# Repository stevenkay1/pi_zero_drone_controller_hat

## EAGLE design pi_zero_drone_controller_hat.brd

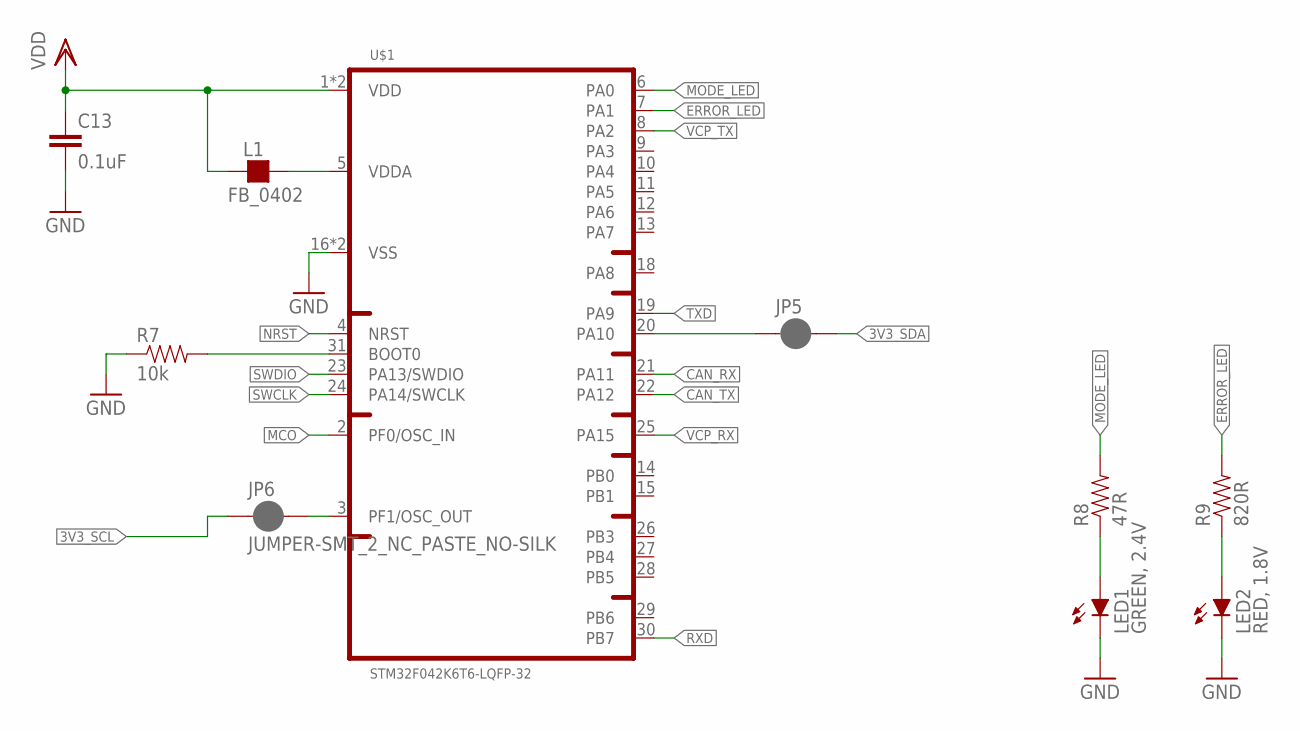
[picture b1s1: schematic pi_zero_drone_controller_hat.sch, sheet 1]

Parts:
C13: 0.1uF; 0402
JP5, JP6: JUMPER-SMT_2_NC_PASTE_NO-SILK; SMT-JUMPER_2_NC_PASTE_NO-SILK
L1: FB_0402; L0402
LED1: GREEN, 2.4V; CHIP-LED0603
LED2: RED, 1.8V; CHIP-LED0603
R7: 10k; RES_0402
R8: 47R; RES_0402
R9: 820R; RES_0402
U$1: STM32F042K6T6-LQFP-32; LQFP-32

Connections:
3V3_SCL: JP6.1; also elsewhere on the board
3V3_SDA: JP5.2; also elsewhere on the board
CAN_RX: U$1.21 (PA11)
CAN_TX: U$1.22 (PA12)
ERROR_LED: R9.2, U$1.7 (PA1)
GND: C13.2, LED1.C, LED2.C, R7.1, U$1.16 (VSS), U$1.32 (VSS); also elsewhere on the board
MCO: U$1.2 (PF0/OSC_IN)
MODE_LED: R8.2, U$1.6 (PA0)
unnamed: R7.2, U$1.31 (BOOT0)
unnamed: L1.2, U$1.5 (VDDA)
unnamed: JP5.1, U$1.20 (PA10)
unnamed: JP6.2, U$1.3 (PF1/OSC_OUT)
unnamed: LED2.A, R9.1
unnamed: LED1.A, R8.1
NRST: U$1.4 (NRST); also elsewhere on the board
RXD: U$1.30 (PB7); also elsewhere on the board
SWCLK: U$1.24 (PA14/SWCLK); also elsewhere on the board
SWDIO: U$1.23 (PA13/SWDIO); also elsewhere on the board
TXD: U$1.19 (PA9); also elsewhere on the board
VCP_RX: U$1.25 (PA15); also elsewhere on the board
VCP_TX: U$1.8 (PA2); also elsewhere on the board
VDD: C13.1, L1.1, U$1.1 (VDD), U$1.17 (VDD); also elsewhere on the board

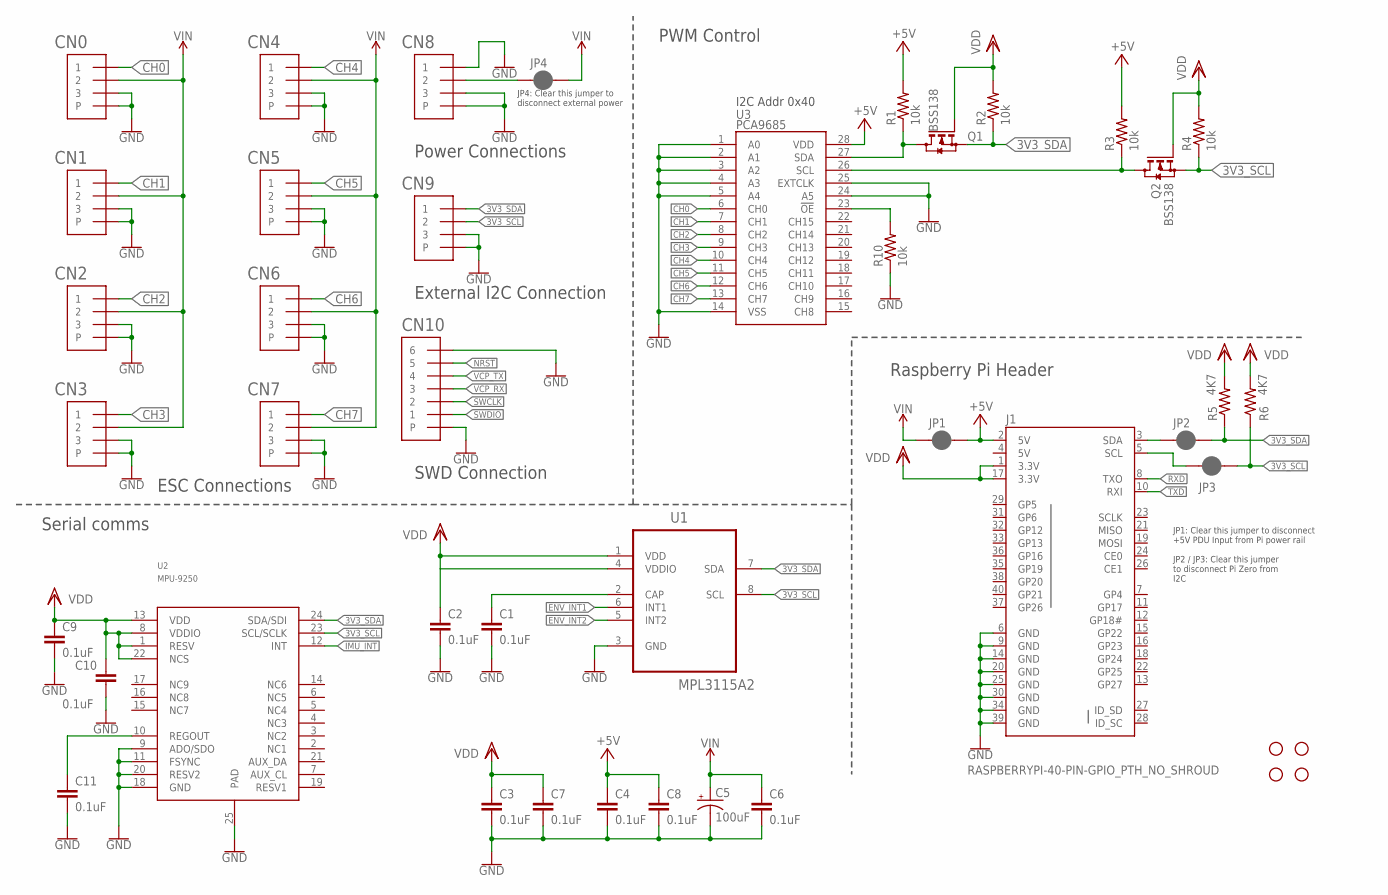
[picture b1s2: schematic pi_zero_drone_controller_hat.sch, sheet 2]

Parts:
C1, C2, C3, C4, C6, C7, C8, C9, C10, C11: 0.1uF; 0402
C5: 100uF; PANASONIC_D
CN0, CN1, CN2, CN3, CN4, CN5, CN6, CN7, CN8, CN9: JST_SH_3
CN10: JST_SH_6
H1, H2, H3, H4: STAND-OFF
J1: RASPBERRYPI-40-PIN-GPIO_PTH_NO_SHROUD; 2X20
JP1, JP2, JP3, JP4: JUMPER-SMT_2_NC_PASTE_NO-SILK; SMT-JUMPER_2_NC_PASTE_NO-SILK
Q1, Q2: BSS138; SOT23
R1, R2, R3, R4, R10: 10k; RES_0402
R5, R6: 4K7; RES_0402
U1: MPL3115A2; DFN300X500X120-8N
U2: MPU-9250; LEAD-QFN24
U3: PCA9685; TSSOP-28_4MM

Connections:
3V3_SCL: CN9.2, JP3.2, Q2.2 (S), R4.1, R6.1, U1.8 (SCL), U2.23 (SCL/SCLK); also elsewhere on the board
3V3_SDA: CN9.1, JP2.2, Q1.2 (S), R2.1, R5.1, U1.7 (SDA), U2.24 (SDA/SDI); also elsewhere on the board
5V: J1.4 (5V)
+5V: C4.1, C8.1, J1.2 (5V), JP1.2, R1.2, R3.2, U3.28 (VDD)
CH0: CN0.1, U3.6 (CH0)
CH1: CN1.1, U3.7 (CH1)
CH2: CN2.1, U3.8 (CH2)
CH3: CN3.1, U3.9 (CH3)
CH4: CN4.1, U3.10 (CH4)
CH5: CN5.1, U3.11 (CH5)
CH6: CN6.1, U3.12 (CH6)
CH7: CN7.1, U3.13 (CH7)
ENV_INT1: U1.6 (INT1)
ENV_INT2: U1.5 (INT2)
GND: C1.2, C2.2, C3.2, C4.2, C5.-, C6.2, C7.2, C8.2, C9.2, C10.2, C11.2, CN0.3, CN0.P$1, CN0.P$2, CN1.3, CN1.P$1, CN1.P$2, CN2.3, CN2.P$1, CN2.P$2, CN3.3, CN3.P$1, CN3.P$2, CN4.3, CN4.P$1, CN4.P$2, CN5.3, CN5.P$1, CN5.P$2, CN6.3, CN6.P$1, CN6.P$2, CN7.3, CN7.P$1, CN7.P$2, CN8.1, CN8.3, CN8.P$1, CN8.P$2, CN9.3, CN9.P$1, CN9.P$2, CN10.6, CN10.P$1, CN10.P$2, J1.6 (GND), J1.9 (GND), J1.14 (GND), J1.20 (GND), J1.25 (GND), J1.30 (GND), J1.34 (GND), J1.39 (GND), R10.1, U1.3 (GND), U2.9 (ADO/SDO), U2.11 (FSYNC), U2.18 (GND), U2.20 (RESV2), U2.25 (PAD), U3.1 (A0), U3.2 (A1), U3.3 (A2), U3.4 (A3), U3.5 (A4), U3.14 (VSS), U3.24 (A5), U3.25 (EXTCLK); also elsewhere on the board
IMU_INT: U2.12 (INT)
unnamed: Q1.3 (D), R1.1, U3.27 (SDA)
unnamed: Q2.3 (D), R3.1, U3.26 (SCL)
unnamed: C11.1, U2.10 (REGOUT)
unnamed: J1.5 (SCL), JP3.1
unnamed: J1.3 (SDA), JP2.1
unnamed: C1.1, U1.2 (CAP)
unnamed: CN8.2, JP4.1
unnamed: R10.2, U3.23 (!OE)
NRST: CN10.5; also elsewhere on the board
RXD: J1.8 (TXO); also elsewhere on the board
SWCLK: CN10.2; also elsewhere on the board
SWDIO: CN10.1; also elsewhere on the board
TXD: J1.10 (RXI); also elsewhere on the board
VCP_RX: CN10.3; also elsewhere on the board
VCP_TX: CN10.4; also elsewhere on the board
VDD: C2.1, C3.1, C7.1, C9.1, C10.1, J1.1 (3.3V), J1.17 (3.3V), Q1.1 (G), Q2.1 (G), R2.2, R4.2, R5.2, R6.2, U1.1 (VDD), U1.4 (VDDIO), U2.1 (RESV), U2.8 (VDDIO), U2.13 (VDD), U2.22 (NCS); also elsewhere on the board
VIN: C5.+, C6.1, CN0.2, CN1.2, CN2.2, CN3.2, CN4.2, CN5.2, CN6.2, CN7.2, JP1.1, JP4.2

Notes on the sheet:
Raspberry Pi Header
Serial comms
PWM Control
ESC Connections
JP1: Clear this jumper to disconnect +5V PDU Input from Pi power rail JP2 / JP3: Clear this jumper to disconnect Pi Zero from I2C
I2C Addr 0x40
Power Connections
External I2C Connection
SWD Connection
JP4: Clear this jumper to disconnect external power

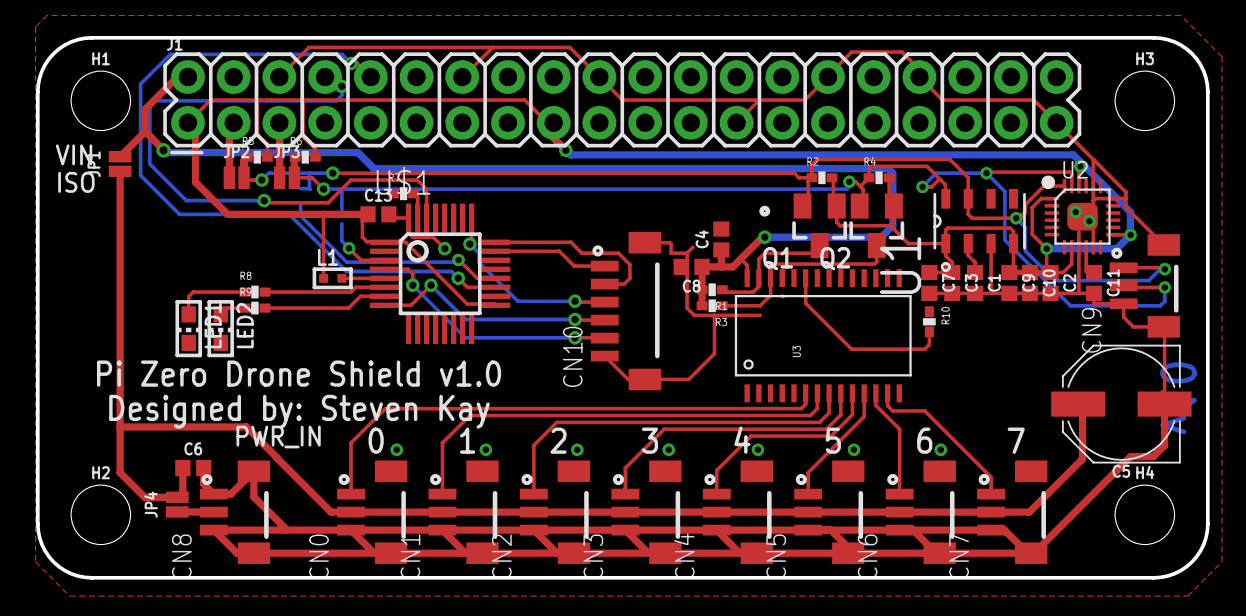
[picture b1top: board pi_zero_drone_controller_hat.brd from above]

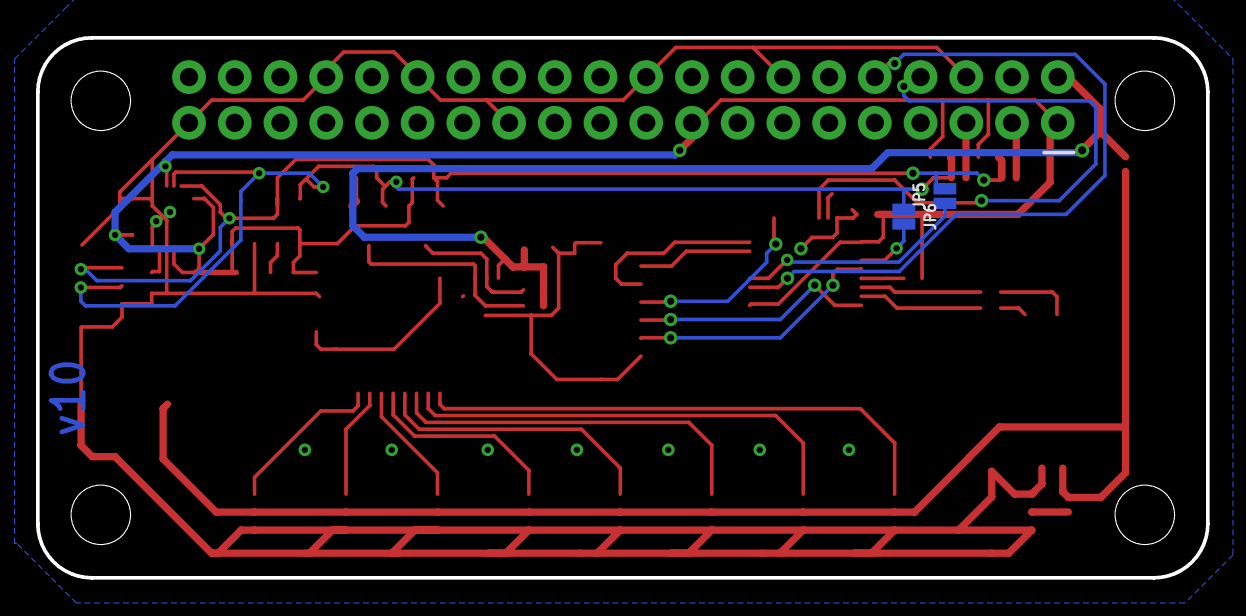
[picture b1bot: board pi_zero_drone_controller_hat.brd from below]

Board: 2 copper layers, 65.0 x 30.0 mm, 53 parts (2 on the bottom side), 37 nets.

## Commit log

2018-03-11 Tidied up repo
2018-03-11 added initial requirements to repo

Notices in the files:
parts and their libraries:
SparkFun-Capacitors: Licensing: Creative Commons ShareAlike 4.0 International - https://creativecommons.org/licenses/by-sa/4.0
